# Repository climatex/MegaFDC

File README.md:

# MegaFDC
Arduino Mega2560 floppy disk controller.

Supports 8" / 5.25" / 3.5" drives (PS/2 2.88MB included) with custom geometry, FAT12 and experimental CP/M.

Interfaces via USB/RS232, also through keyboard and display.

# More information
Check out my [website article](http://boginjr.com/it/hw/megafdc) to learn more!

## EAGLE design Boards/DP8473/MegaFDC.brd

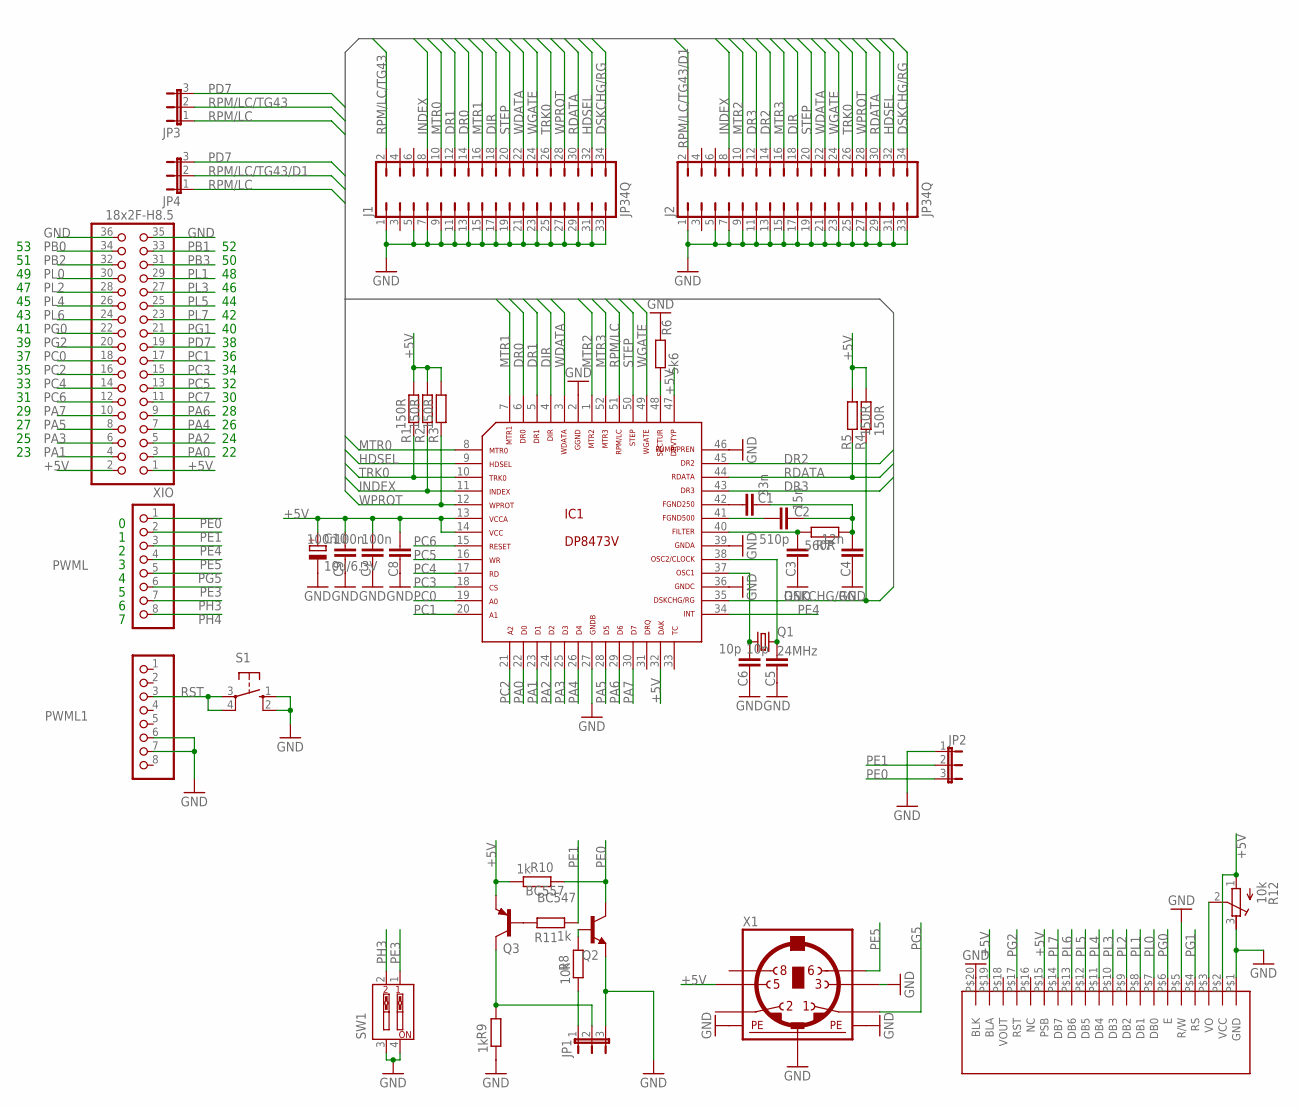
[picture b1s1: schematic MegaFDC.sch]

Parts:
C1: 33n; C025-025X050
C2: 15n; C025-025X050
C3: 510p; C025-025X050
C4: 12n; C025-025X050
C5, C6: 10p; C025-025X050
C7, C8, C9: 100n; C050-025X075
C10: 10u/6.3V; B45181A
IC1: DP8473V; S52
J1, J2: JP34Q
JP1, JP2, JP3, JP4: JP2E; JP2
PWML, PWML1: 8x1F-H8.5; 1X08
Q1: 24MHz; HC49/S
Q2: BC547; TO92S
Q3: BC557; TO92-EBC
R1, R2, R3, R4, R5: 150R; 0207/7
R6: 5k6; 0207/7
R7: 560R; 0207/7
R8: 10k; 0207/7
R9, R10, R11: 1k; 0207/7
R12: 10k; RTRIM3296Y
S1: 10-XX; B3F-10XX
SW1: DIP2X; EDG-02
U$1: W12864
X1: MINI_DIN_6; M_DIN6
XIO: 18x2F-H8.5; 2X18

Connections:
+5V: C7.2, C8.2, C9.2, C10.+, IC1.13, IC1.14, IC1.32, IC1.47, Q3.E, R1.2, R2.2, R3.2, R4.2, R5.2, R10.1, R12.1 (A), U$1.P$2 (VCC), U$1.P$15 (PSB), U$1.P$19 (BLA), X1.5, XIO.1, XIO.2
DIR: IC1.4, J1.18, J2.18
DR0: IC1.6, J1.14
DR1: IC1.5, J1.12
DR2: IC1.45, J2.14
DR3: IC1.43, J2.12
DSKCHG/RG: IC1.35, J1.34, J2.34, R4.1
GND: C3.1, C4.1, C5.1, C6.1, C7.1, C8.1, C9.1, C10.-, IC1.2, IC1.27, IC1.36, IC1.39, IC1.46, J1.1, J1.5, J1.7, J1.9, J1.11, J1.13, J1.15, J1.17, J1.19, J1.21, J1.23, J1.25, J1.27, J1.29, J1.31, J1.33, J2.1, J2.5, J2.7, J2.9, J2.11, J2.13, J2.15, J2.17, J2.19, J2.21, J2.23, J2.25, J2.27, J2.29, J2.31, J2.33, JP1.3, JP2.1, PWML1.6, PWML1.7, Q2.1 (E), R6.2, R9.1, R12.3 (E), S1.1 (S), S1.2 (S1), SW1.3, SW1.4, U$1.P$1 (GND), U$1.P$5 (R/W), U$1.P$20 (BLK), X1.3, X1.SH1 (PE1), X1.SH2 (PE2), X1.SH3 (PE3), XIO.35, XIO.36
HDSEL: IC1.9, J1.32, J2.32
INDEX: IC1.11, J1.8, J2.8, R2.1
MTR0: IC1.8, J1.10
MTR1: IC1.7, J1.16
MTR2: IC1.1, J2.10
MTR3: IC1.52, J2.16
unnamed: C1.1, IC1.42
unnamed: C2.1, IC1.41
unnamed: C1.2, C2.2, C4.2, R7.2
unnamed: C3.2, IC1.40, R7.1
unnamed: C5.2, IC1.38, Q1.2
unnamed: IC1.48, R6.1
unnamed: C6.2, IC1.37, Q1.1
unnamed: JP1.1, R8.1
unnamed: Q2.2 (B), R8.2
unnamed: JP1.2, Q3.C, R9.2
unnamed: Q3.B, R11.2
unnamed: R12.2 (S), U$1.P$3 (VO)
PA0: IC1.22, XIO.3
PA1: IC1.23, XIO.4
PA2: IC1.24, XIO.5
PA3: IC1.25, XIO.6
PA4: IC1.26, XIO.7
PA5: IC1.28, XIO.8
PA6: IC1.29, XIO.9
PA7: IC1.30, XIO.10
PB0: XIO.34
PB1: XIO.33
PB2: XIO.32
PB3: XIO.31
PC0: IC1.19, XIO.18
PC1: IC1.20, XIO.17
PC2: IC1.21, XIO.16
PC3: IC1.18, XIO.15
PC4: IC1.17, XIO.14
PC5: IC1.16, XIO.13
PC6: IC1.15, XIO.12
PC7: XIO.11
PD7: JP3.3, JP4.3, XIO.19
PE0: JP2.3, PWML.1, Q2.3 (C), R10.2
PE1: JP2.2, PWML.2, R11.1
PE3: PWML.6, SW1.1
PE4: IC1.34, PWML.3
PE5: PWML.4, X1.6
PG0: U$1.P$6 (E), XIO.22
PG1: U$1.P$4 (RS), XIO.21
PG2: U$1.P$17 (RST), XIO.20
PG5: PWML.5, X1.1
PH3: PWML.7, SW1.2
PH4: PWML.8
PL0: U$1.P$7 (DB0), XIO.30
PL1: U$1.P$8 (DB1), XIO.29
PL2: U$1.P$9 (DB2), XIO.28
PL3: U$1.P$10 (DB3), XIO.27
PL4: U$1.P$11 (DB4), XIO.26
PL5: U$1.P$12 (DB5), XIO.25
PL6: U$1.P$13 (DB6), XIO.24
PL7: U$1.P$14 (DB7), XIO.23
RDATA: IC1.44, J1.30, J2.30, R5.1
RPM/LC: IC1.51, JP3.1, JP4.1
RPM/LC/TG43: J1.2, JP3.2
RPM/LC/TG43/D1: J2.2, JP4.2
RST: PWML1.3, S1.3, S1.4 (P1)
STEP: IC1.50, J1.20, J2.20
TRK0: IC1.10, J1.26, J2.26, R1.1
WDATA: IC1.3, J1.22, J2.22
WGATE: IC1.49, J1.24, J2.24
WPROT: IC1.12, J1.28, J2.28, R3.1

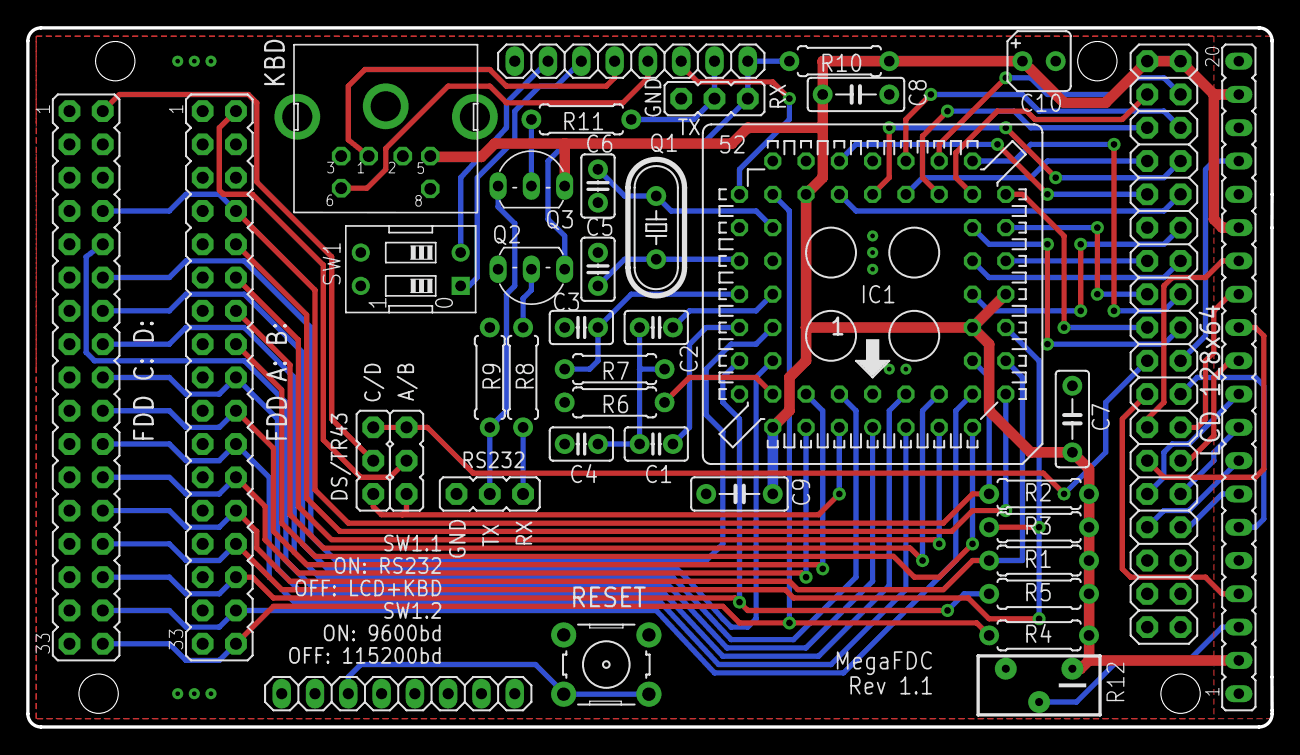
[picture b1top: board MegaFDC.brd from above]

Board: 2 copper layers, 94.9 x 53.3 mm, 39 parts (0 on the bottom side), 70 nets.

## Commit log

2023-03-14 Unset FDC_ISR_ASSEMBLY by default
2023-03-15 Fix double-stepping
2023-07-04 Handle TG43 on PD7, wait 2 cycles for FDC, CP/M root dir bugfixes
2023-07-24 Do seek test on drive select, comment on TG43 in config.h
2023-08-18 Add boards and schematics, FIFO buffer support, perpendicular recording, bugfixes
2023-08-28 Update web links, inform about formatting with verify if writing filesystem
2023-08-30 Speed up FAT file I/O by turning off the Tiny buffer
2024-11-24 Add ImageDisk (IMD) support, bugfixes
2024-11-28 Set stepper to 16ms for an 8" CDC drive, bugfix in DRIVPARM
2025-03-30 Improve interleave detection in IMD mode; bugfixes
2025-05-26 Build 26th of May 2025 changes:
    - UI with LCD output now doesn't require a physical keyboard,
    - TYPEINTO command opens files with append instead of truncate,
    - bugfix in the DELAY_MS macro,
    - DP8473 Kicad schematic parts numbers reordered to match the Eagle PCB.
2025-06-26 Build 26th of June 2025 changes:
    - IMD mode: sector 0 compatibility,
    - IMD mode format command: customizable starting sector,
    - both modes: better distinguish between track and a cylinder in code and strings.
2025-06-27 Sync with Winchesterduino
2025-07-21 Classic mode: bugfix in getMaximumSectorCount()
2026-02-22 Add SD support, remember settings in IMD mode, bugfixes
2026-02-27 Small fix for Num Lock
